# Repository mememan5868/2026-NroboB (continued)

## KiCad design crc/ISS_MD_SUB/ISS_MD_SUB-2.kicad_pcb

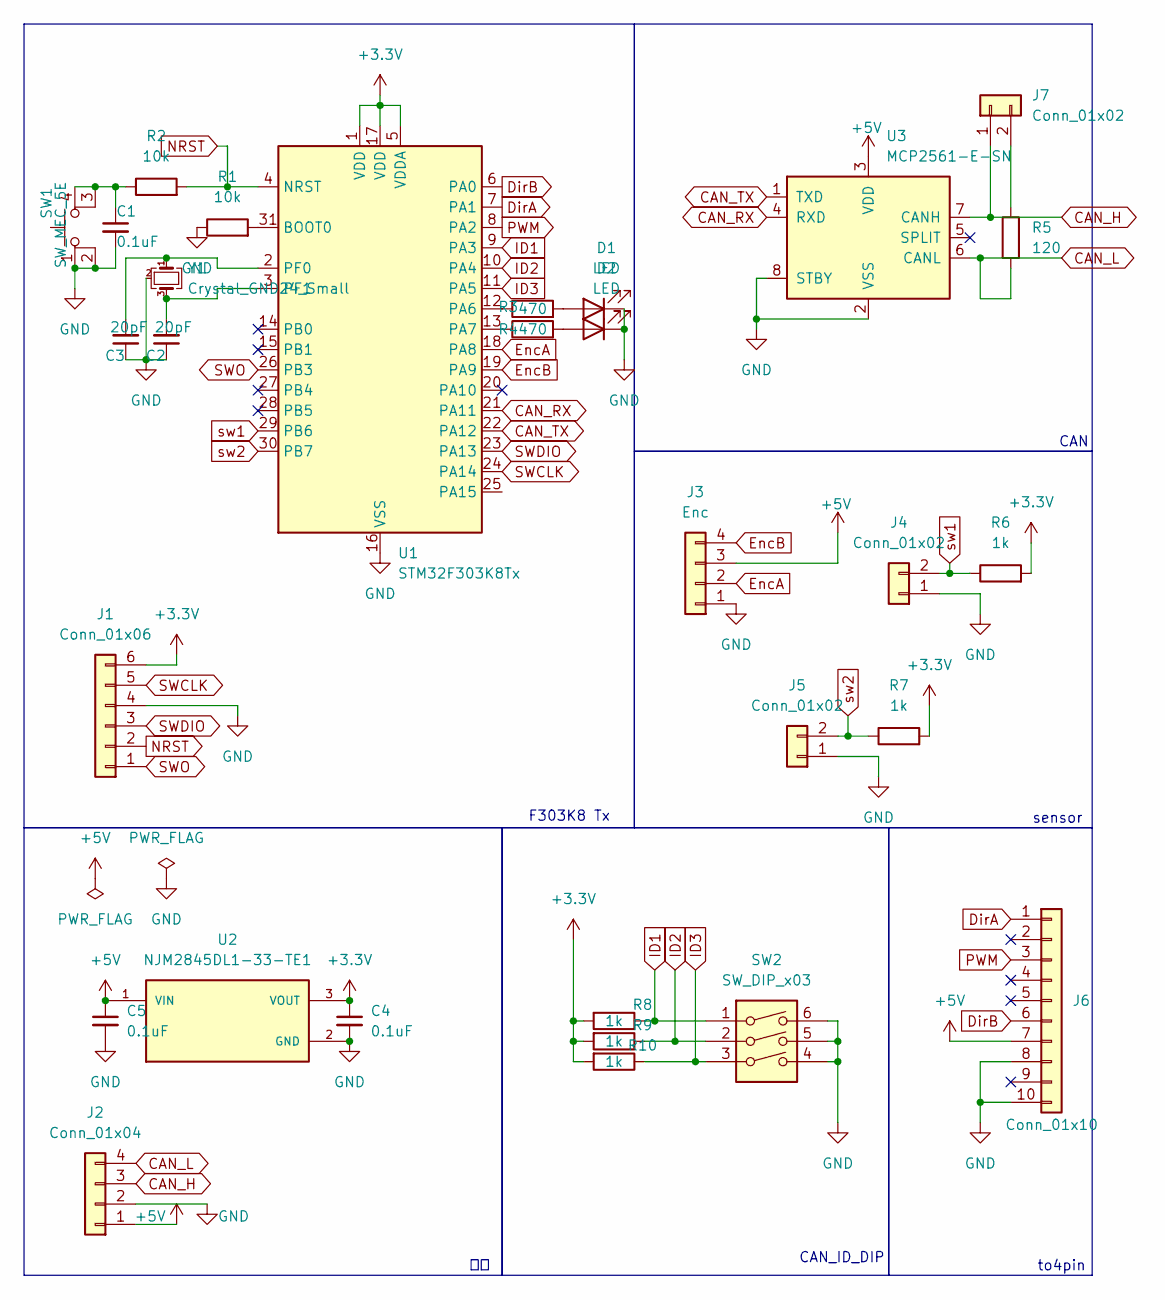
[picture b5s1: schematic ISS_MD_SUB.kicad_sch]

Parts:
C1, C4, C5: 0.1uF; C_0603_1608Metric_Pad1.08x0.95mm_HandSolder
C2, C3: 20pF; C_0603_1608Metric_Pad1.08x0.95mm_HandSolder
D1, D2: LED; LED_0603_1608Metric_Pad1.05x0.95mm_HandSolder
J1: Conn_01x06; PinHeader_1x06_P2.54mm_Vertical
J2: Conn_01x04; JST_XH_S4B-XH-A_1x04_P2.50mm_Horizontal
J3: Enc; JST_XH_S4B-XH-A_1x04_P2.50mm_Horizontal
J4, J5: Conn_01x02; JST_XH_B2B-XH-A_1x02_P2.50mm_Vertical
J6: Conn_01x10; PinSocket_1x10_P2.54mm_Vertical
J7: Conn_01x02; PinHeader_1x02_P2.54mm_Vertical
R1, R2: 10k; R_0603_1608Metric_Pad0.98x0.95mm_HandSolder
R3, R4: 470; R_0603_1608Metric_Pad0.98x0.95mm_HandSolder
R5: 120; R_0603_1608Metric_Pad0.98x0.95mm_HandSolder
R6, R7, R8, R9, R10: 1k; R_0603_1608Metric_Pad0.98x0.95mm_HandSolder
SW1: SW_MEC_5E; SW4_SKRPABE010_ALPS
SW2: SW_DIP_x03; SW_DIP_SPSTx03_Slide_9.78x9.8mm_W7.62mm_P2.54mm
U1: STM32F303K8Tx; LQFP-32_7x7mm_P0.8mm
U2: NJM2845DL1-33-TE1; DPAK228P968X238-4N; PARTREV 2012-10-31
U3: MCP2561-E-SN; SOIC-8_3.9x4.9mm_P1.27mm
Y1: Crystal_GND24_Small; XTAL_TSX-3225_25.0000MF10P-C0

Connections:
+3.3V: C4.1, J1.6, R6.2, R7.2, R8.2, R9.2, R10.2, U1.1 (VDD), U1.5 (VDDA), U1.17 (VDD), U2.3 (VOUT)
+5V: C5.1, J2.1, J3.3, J6.7, U2.1 (VIN), U3.3 (VDD)
CAN_H: J2.3, J7.1, U3.7 (CANH)
CAN_L: J2.4, R5.2, U3.6 (CANL)
CAN_RX: U1.21 (PA11), U3.4 (RXD)
CAN_TX: U1.22 (PA12), U3.1 (TXD)
DirA: J6.1, U1.7 (PA1)
DirB: J6.6, U1.6 (PA0)
EncA: J3.2, U1.18 (PA8)
EncB: J3.4, U1.19 (PA9)
GND: C1.2, C2.1, C3.1, C4.2, C5.2, D1.1 (K), D2.1 (K), J1.4, J2.2, J3.1, J4.1, J5.1, J6.8, J6.10, R1.1, SW1.1, SW1.2, SW2.4, SW2.5, SW2.6, U1.16 (VSS), U1.32 (VSS), U2.2 (GND), U3.2 (VSS), U3.8 (STBY), Y1.2 (G), Y1.4 (G)
ID1: R8.1, SW2.1, U1.9 (PA3)
ID2: R9.1, SW2.2, U1.10 (PA4)
ID3: R10.1, SW2.3, U1.11 (PA5)
NRST: J1.2, R2.2, U1.4 (NRST)
unnamed: D1.2 (A), R3.2
unnamed: D2.2 (A), R4.2
unnamed: J7.2, R5.1
unnamed: C1.1, R2.1, SW1.3 (K), SW1.4 (A)
unnamed: R1.2, U1.31 (BOOT0)
unnamed: R3.1, U1.12 (PA6)
unnamed: R4.1, U1.13 (PA7)
unnamed: C3.2, U1.2 (PF0), Y1.1
unnamed: C2.2, U1.3 (PF1), Y1.3
PWM: J6.3, U1.8 (PA2)
SWCLK: J1.5, U1.24 (PA14)
SWDIO: J1.3, U1.23 (PA13)
SWO: J1.1, U1.26 (PB3)
sw1: J4.2, R6.1, U1.29 (PB6)
sw2: J5.2, R7.1, U1.30 (PB7)

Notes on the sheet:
CAN
F303K8 Tx
sensor
CAN_ID_DIP
to4pin

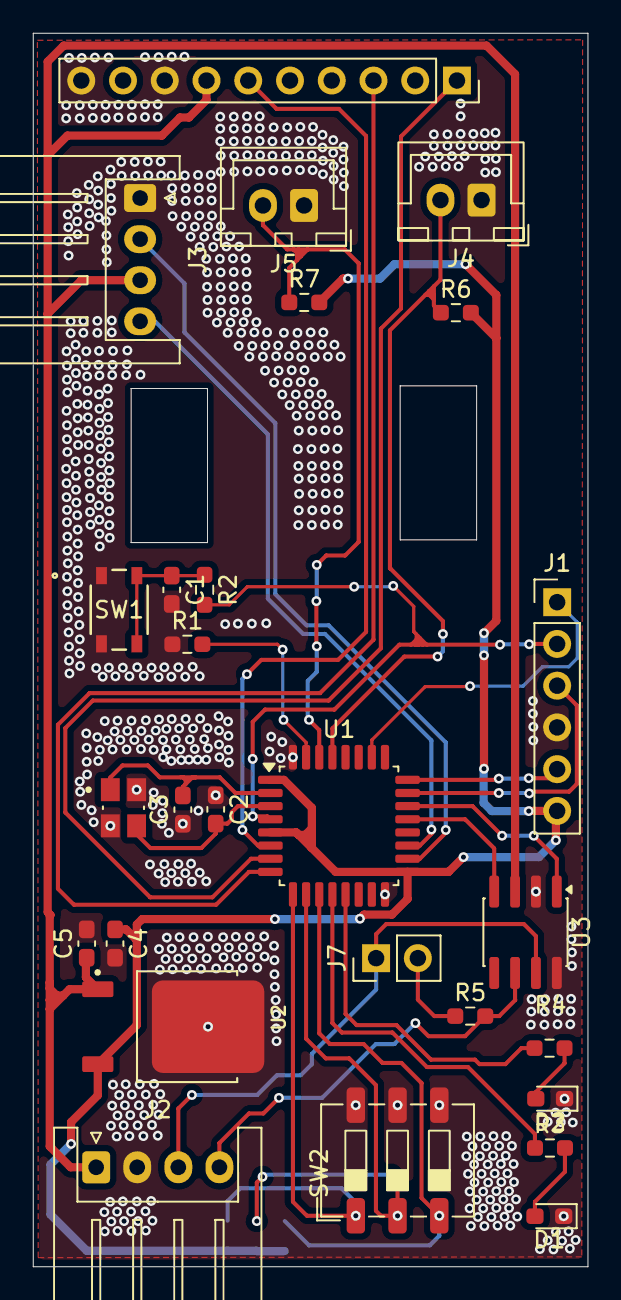
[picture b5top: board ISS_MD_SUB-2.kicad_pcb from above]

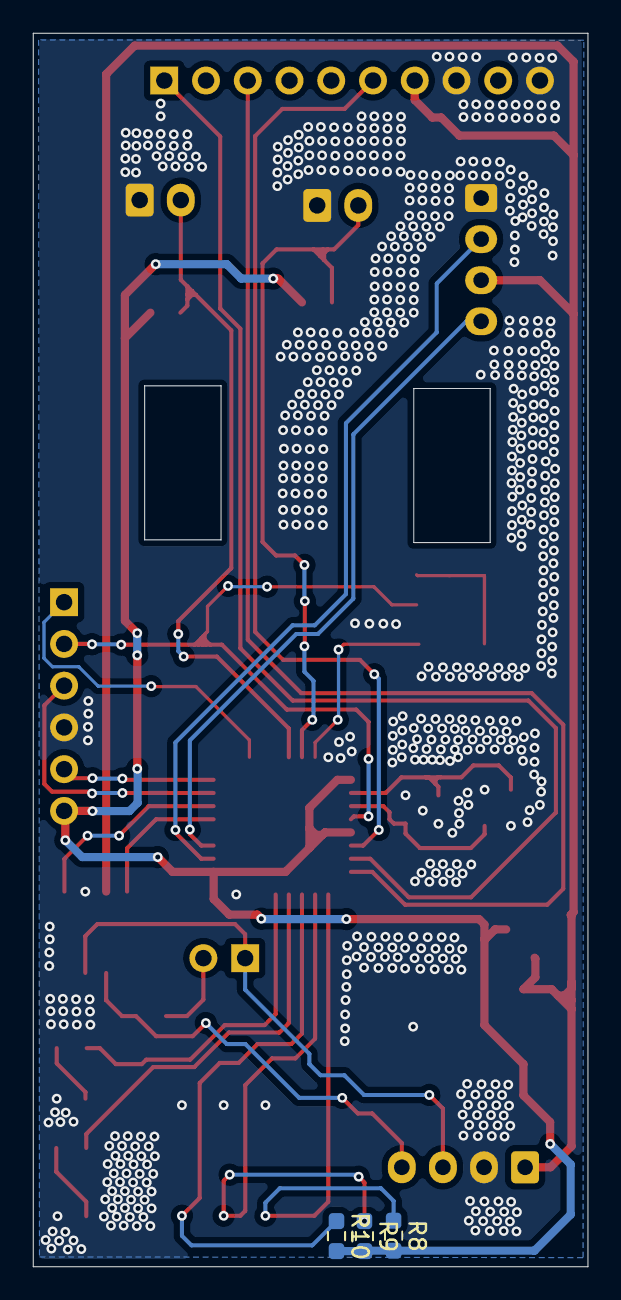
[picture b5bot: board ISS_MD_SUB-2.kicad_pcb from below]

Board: 2 copper layers, 33.7 x 75.0 mm, 30 parts (3 on the bottom side), 30 nets.

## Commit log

2026-04-10 ディレクトリ追加
2026-04-13 基板2枚め
2026-04-22 ノード基板追加
2026-05-07 ノード完成
2026-05-07 MD-SUB再設計多すぎだろFUCK！！！！！
2026-05-10 ガーバーファイル生成
2026-05-10 ガーバーまとめ
2026-05-10 ガーバー再生成
2026-05-10 ガーバー再まとめ
2026-05-11 MDSUBのガーバー再生成
